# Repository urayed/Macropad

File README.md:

[BOM.csv](https://github.com/user-attachments/files/29574119/BOM.csv)
# Macropad
This is Macropad version 1.

The Macropad has: 
1. 9 MX Keys
2. 1 OLED Screen
3. 1 Rotary Encoder
4. 1 3x3 LED Matrix

As of now, the firmware is likely very bare bones. For the future, I plan to create custom software for programming the keyboard without code. I also want to be able to control the OLED screen and LED Matrix for future projects, so that is also a project, itself, to work on.
#
# The Case
The case uses 6 M3x16mm screws and is comprised of 2 parts. 

 Will be fully 3D Printed.
#
# The PCB
The PCB is made fully in KiCad.

The schematic:

# BOM
Seeed XIAO RP2040 x1 

1N4148 x9 

MX-Switches x9 

EC11 x1 

OLED x1 

DSA Keycaps x9 

SK6812 x9 

M3x16mm x6 

M3x5mx4mm Headset x0-6

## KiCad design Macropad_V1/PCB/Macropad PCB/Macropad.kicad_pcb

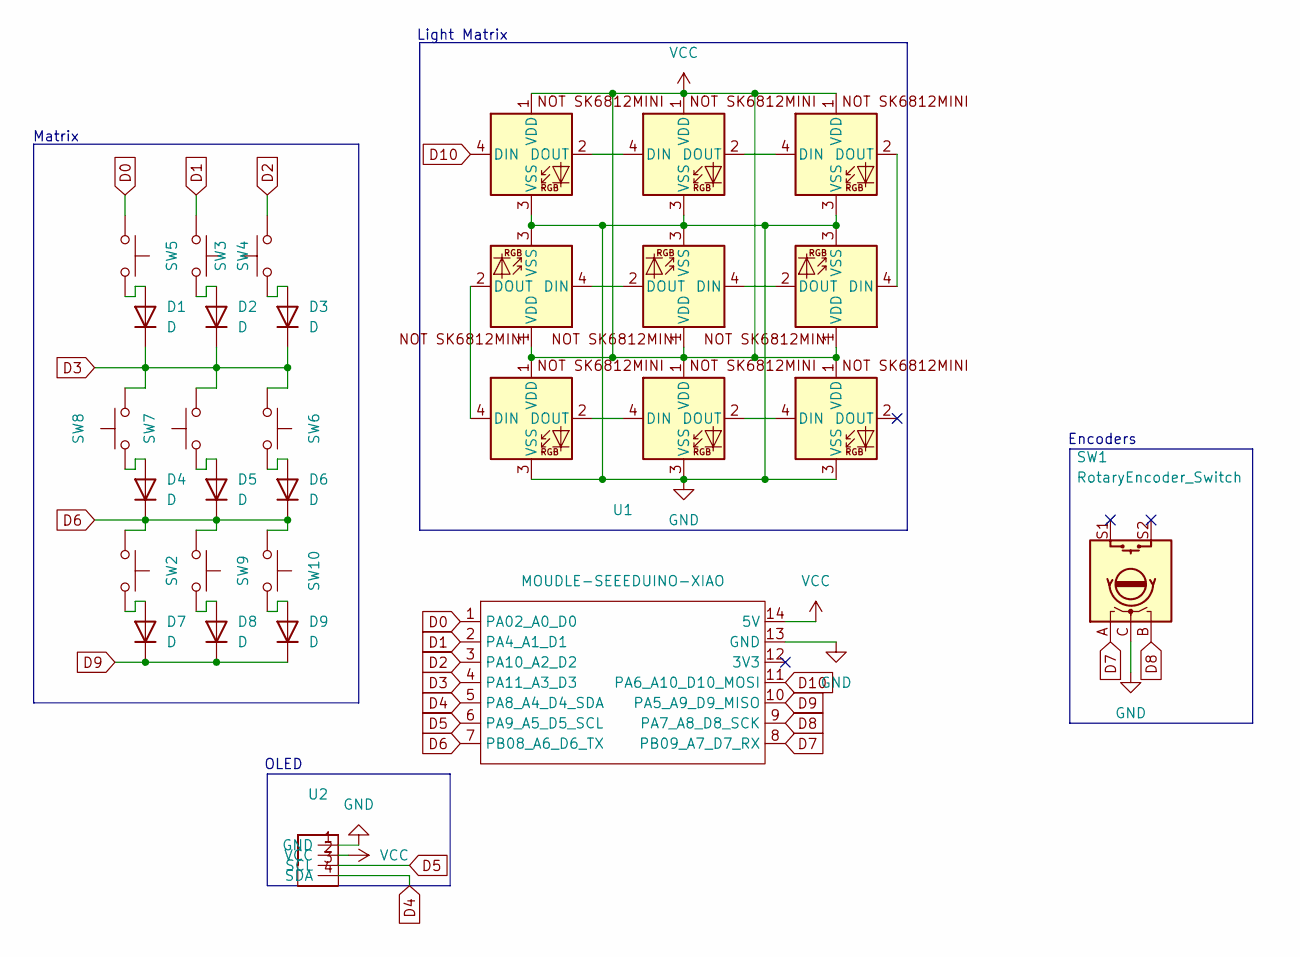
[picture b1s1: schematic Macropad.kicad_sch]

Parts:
D1, D2, D3, D4, D5, D6, D7, D8, D9: D; D_DO-35_SOD27_P10.16mm_Horizontal
D10, D11, D12, D13, D14, D15, D16, D17, D18: SK6812MINI-E; SK6812MINI-E_fixed
SW1: RotaryEncoder_Switch; RotaryEncoder_Alps_EC11E-Switch_Vertical_H20mm_CircularMoun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
SW2, SW3, SW4, SW5, SW6, SW7, SW8, SW9, SW10: SW_Push; MX-Solderable-1U
U1: MOUDLE-SEEEDUINO-XIAO; XIAO-Generic-Hybrid-14P-2.54-21X17.8MM
U2: SSD1306-0.91-OLED-4pin-128x32

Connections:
D0: SW5.1, U1.1 (PA02_A0_D0)
D1: SW4.1, U1.2 (PA4_A1_D1)
D2: SW3.1, U1.3 (PA10_A2_D2)
D3: D1.1 (K), D2.1 (K), D3.1 (K), SW6.1, SW7.1, SW8.1, U1.4 (PA11_A3_D3)
D4: U1.5 (PA8_A4_D4_SDA), U2.4 (SDA)
D5: U1.6 (PA9_A5_D5_SCL), U2.3 (SCL)
D6: D4.1 (K), D5.1 (K), D6.1 (K), SW2.1, SW9.1, SW10.1, U1.7 (PB08_A6_D6_TX)
D7: SW1.A, U1.8 (PB09_A7_D7_RX)
D8: SW1.B, U1.9 (PA7_A8_D8_SCK)
D9: D7.1 (K), D8.1 (K), D9.1 (K), U1.10 (PA5_A9_D9_MISO)
D10: D10.4 (DIN), U1.11 (PA6_A10_D10_MOSI)
GND: D10.3 (VSS), D11.3 (VSS), D12.3 (VSS), D13.3 (VSS), D14.3 (VSS), D15.3 (VSS), D16.3 (VSS), D17.3 (VSS), D18.3 (VSS), SW1.C, U1.13 (GND), U2.1 (GND)
unnamed: D1.2 (A), SW5.2
unnamed: D2.2 (A), SW4.2
unnamed: D3.2 (A), SW3.2
unnamed: D4.2 (A), SW8.2
unnamed: D5.2 (A), SW7.2
unnamed: D6.2 (A), SW6.2
unnamed: D7.2 (A), SW2.2
unnamed: D8.2 (A), SW9.2
unnamed: D9.2 (A), SW10.2
unnamed: D10.2 (DOUT), D11.4 (DIN)
unnamed: D11.2 (DOUT), D12.4 (DIN)
unnamed: D12.2 (DOUT), D13.4 (DIN)
unnamed: D13.2 (DOUT), D14.4 (DIN)
unnamed: D14.2 (DOUT), D15.4 (DIN)
unnamed: D15.2 (DOUT), D16.4 (DIN)
unnamed: D16.2 (DOUT), D17.4 (DIN)
unnamed: D17.2 (DOUT), D18.4 (DIN)
VCC: D10.1 (VDD), D11.1 (VDD), D12.1 (VDD), D13.1 (VDD), D14.1 (VDD), D15.1 (VDD), D16.1 (VDD), D17.1 (VDD), D18.1 (VDD), U1.14 (5V), U2.2 (VCC)

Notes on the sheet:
OLED
Encoders
Light Matrix
Matrix

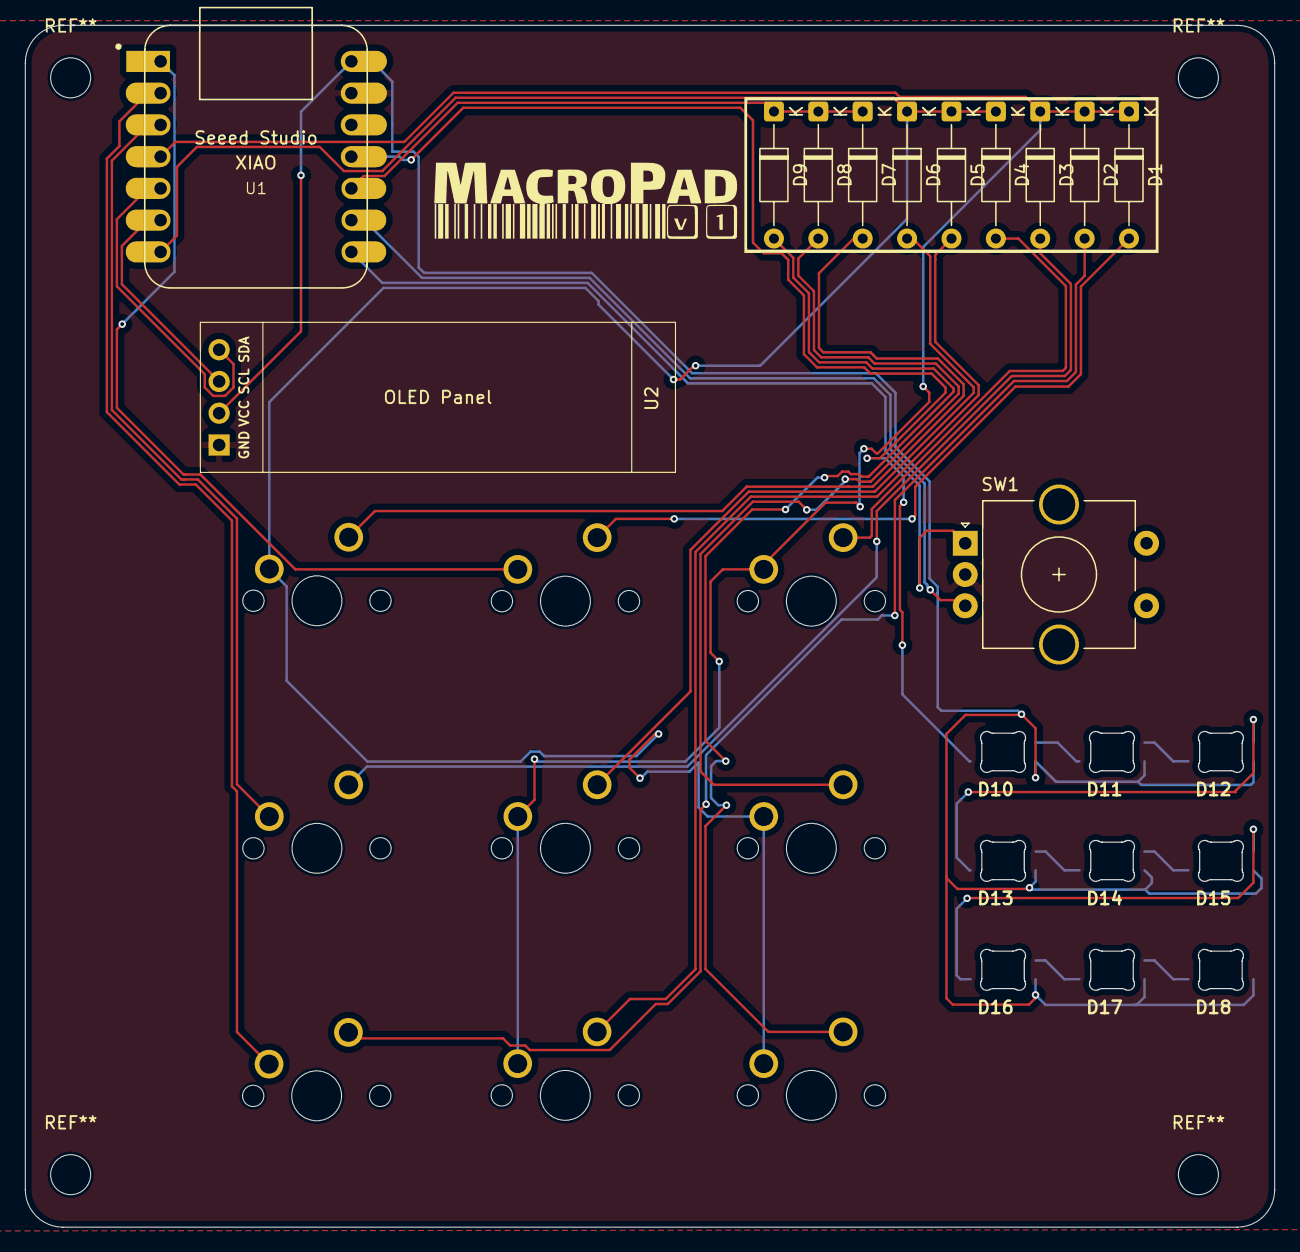
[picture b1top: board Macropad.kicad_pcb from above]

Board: 2 copper layers, 99.9 x 96.1 mm, 30 parts (0 on the bottom side), 30 nets.
